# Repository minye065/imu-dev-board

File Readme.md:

\# Imu dev board

A devboard that lets you test imu programs via the onboard imu and being able to test data to it

\*Powered via the usb cable

Features:
RP2350A - MCU
ICM-42688-P - IMU

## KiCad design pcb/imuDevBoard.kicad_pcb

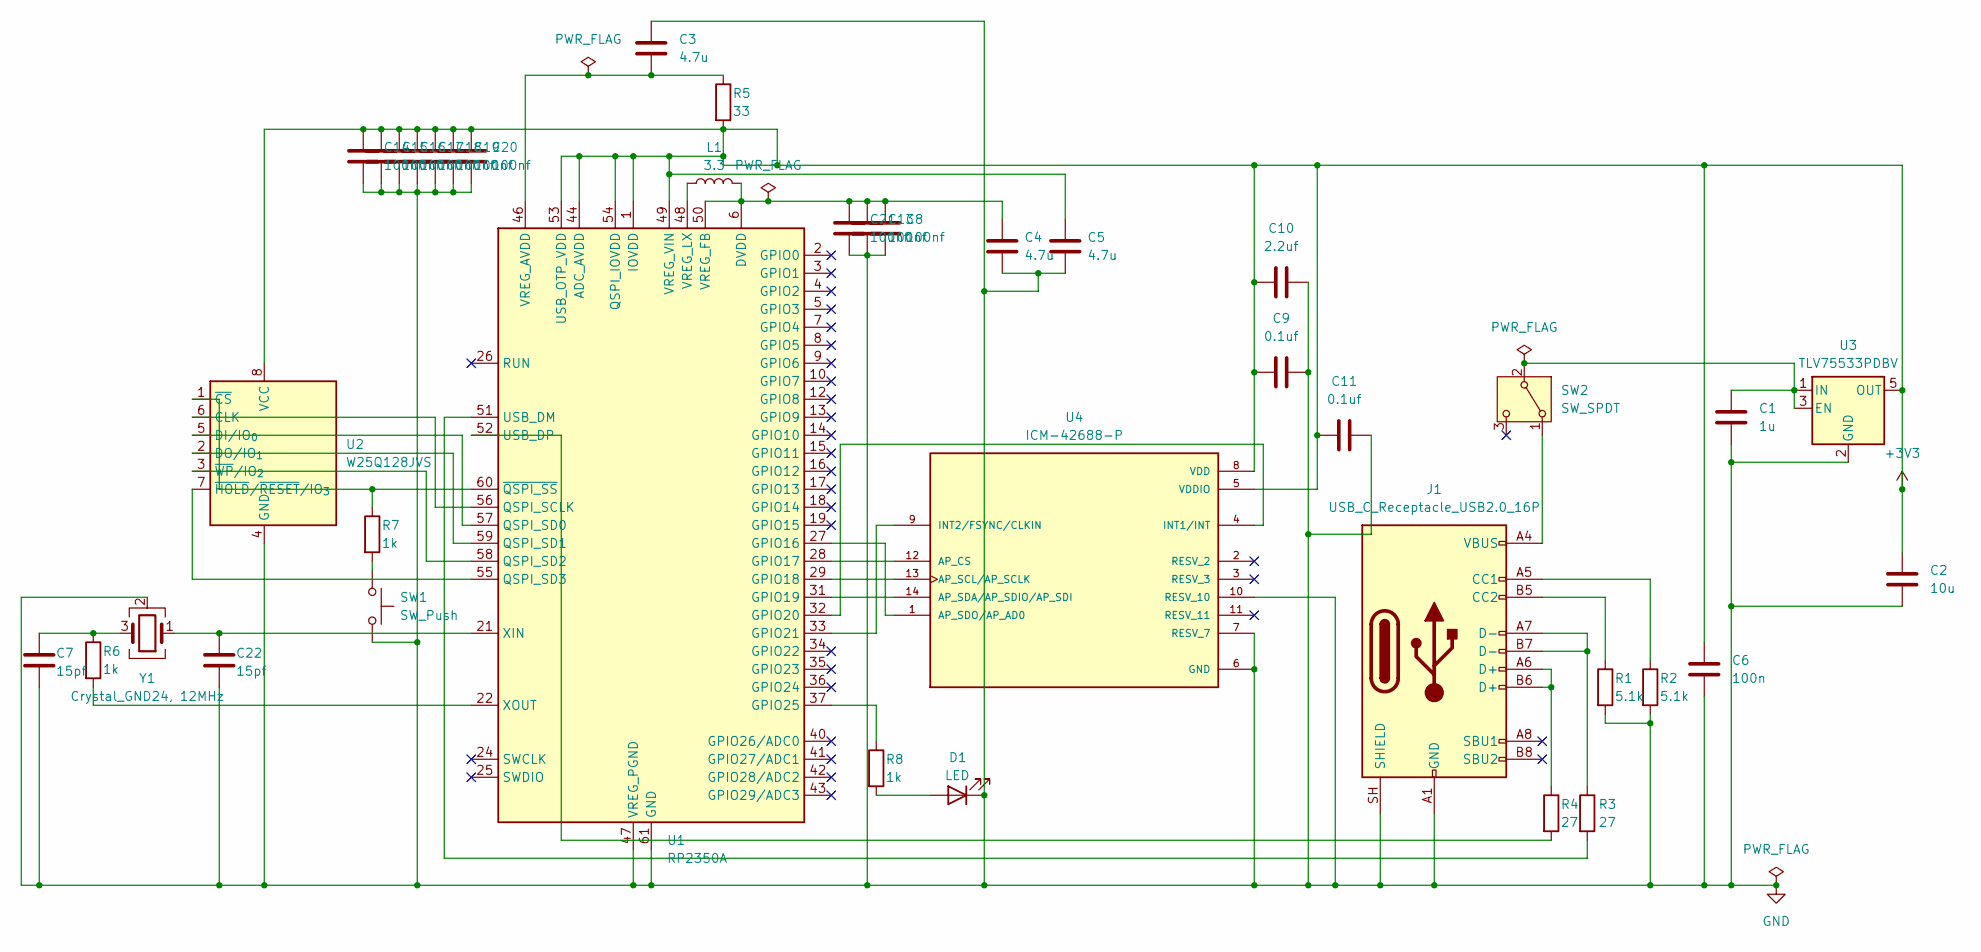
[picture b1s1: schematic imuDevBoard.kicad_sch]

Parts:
C1: 1u; C_0402_1005Metric
C2: 10u; C_0603_1608Metric
C3, C4, C5: 4.7u; C_0402_1005Metric
C6: 100n; C_0402_1005Metric
C7, C22: 15pf; C_0402_1005Metric
C8, C13, C14, C15, C16, C17, C18, C19, C20, C21: 100nf; C_0402_1005Metric
C9, C11: 0.1uf; C_0402_1005Metric
C10: 2.2uf; C_0402_1005Metric
D1: LED; LED_0603_1608Metric
J1: USB_C_Receptacle_USB2.0_16P; USB_C_Receptacle_HRO_TYPE-C-31-M-12
L1: 3.3; AOTA-B2016
R1, R2: 5.1k; R_0402_1005Metric
R3, R4: 27; R_0402_1005Metric
R5: 33; R_0402_1005Metric
R6, R7, R8: 1k; R_0402_1005Metric
SW1: SW_Push; SW_Push_1P1T_NO_Vertical_Wuerth_434133025816
SW2: SW_SPDT; SW_SPDT_Shouhan_MSK12C02
U1: RP2350A; QFN-60-1EP_7x7mm_P0.4mm_EP3.4x3.4mm
U2: W25Q128JVS; SOIC-8_5.3x5.3mm_P1.27mm
U3: TLV75533PDBV; SOT-23-5
U4: ICM-42688-P; PARTREV 1.2
Y1: Crystal_GND24, 12MHz; Crystal_SMD_3225-4Pin_3.2x2.5mm

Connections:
+3V3: C2.1, C5.2, C6.2, C9.1, C10.1, C11.1, C14.2, C15.2, C16.2, C17.2, C18.2, C19.2, C20.2, R5.2, U1.1 (IOVDD), U1.11 (IOVDD), U1.20 (IOVDD), U1.30 (IOVDD), U1.38 (IOVDD), U1.44 (ADC_AVDD), U1.45 (IOVDD), U1.49 (VREG_VIN), U1.53 (USB_OTP_VDD), U1.54 (QSPI_IOVDD), U2.8 (VCC), U3.5 (OUT), U4.5 (VDDIO), U4.8 (VDD)
GND: C1.2, C2.2, C3.1, C4.1, C5.1, C6.1, C7.1, C8.1, C9.2, C10.2, C11.2, C13.1, C14.1, C15.1, C16.1, C17.1, C18.1, C19.1, C20.1, C21.1, C22.1, D1.1 (K), J1.A1 (GND), J1.A12 (GND), J1.B1 (GND), J1.B12 (GND), J1.SH (SHIELD), R1.2, R2.2, SW1.2, U1.47 (VREG_PGND), U1.61 (GND), U2.4 (GND), U3.2 (GND), U4.6 (GND), U4.7 (RESV_7), U4.10 (RESV_10), Y1.2 (G), Y1.4 (G)
unnamed: C7.2, R6.1, Y1.3
unnamed: D1.2 (A), R8.2
unnamed: J1.A5 (CC1), R2.1
unnamed: J1.B5 (CC2), R1.1
unnamed: J1.A6 (D+), J1.B6 (D+), R4.1
unnamed: J1.A7 (D-), J1.B7 (D-), R3.1
unnamed: R7.2, SW1.1
unnamed: J1.A4 (VBUS), J1.A9 (VBUS), J1.B4 (VBUS), J1.B9 (VBUS), SW2.1 (A)
unnamed: C1.1, SW2.2 (B), U3.1 (IN), U3.3 (EN)
unnamed: U1.27 (GPIO16), U4.1 (AP_SDO/AP_AD0)
unnamed: U1.28 (GPIO17), U4.12 (AP_CS)
unnamed: U1.29 (GPIO18), U4.13 (AP_SCL/AP_SCLK)
unnamed: U1.31 (GPIO19), U4.14 (AP_SDA/AP_SDIO/AP_SDI)
unnamed: U1.32 (GPIO20), U4.4 (INT1/INT)
unnamed: U1.33 (GPIO21), U4.9 (INT2/FSYNC/CLKIN)
unnamed: R8.1, U1.37 (GPIO25)
unnamed: U1.56 (QSPI_SCLK), U2.6 (CLK)
unnamed: U1.57 (QSPI_SD0), U2.5 (DI/IO_{0})
unnamed: U1.59 (QSPI_SD1), U2.2 (DO/IO_{1})
unnamed: U1.58 (QSPI_SD2), U2.3 (~WP/IO_{2})
unnamed: U1.55 (QSPI_SD3), U2.7 (~HOLD/~RESET/IO_{3})
unnamed: R3.2, U1.51 (USB_DM)
unnamed: R4.2, U1.52 (USB_DP)
unnamed: C3.2, R5.1, U1.46 (VREG_AVDD)
unnamed: C4.2, C8.2, C13.2, C21.2, L1.2, U1.6 (DVDD), U1.23 (DVDD), U1.39 (DVDD), U1.50 (VREG_FB)
unnamed: L1.1, U1.48 (VREG_LX)
unnamed: C22.2, U1.21 (XIN), Y1.1
unnamed: R6.2, U1.22 (XOUT)
unnamed: R7.1, U1.60 (~QSPI_SS), U2.1 (~CS)

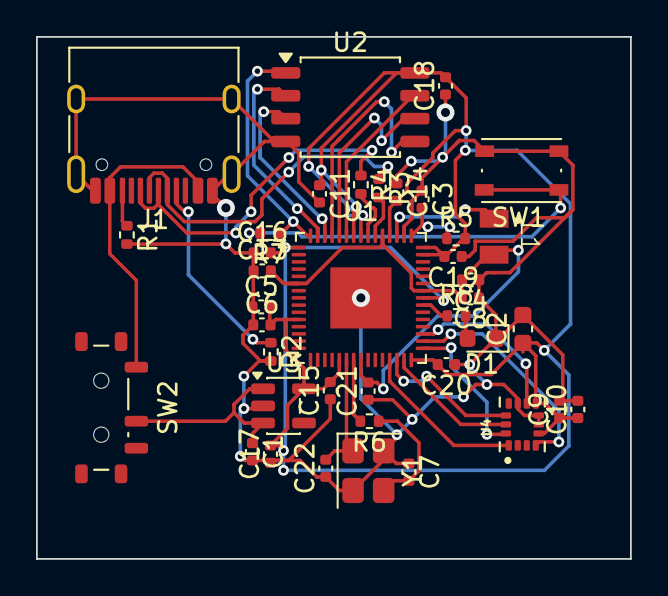
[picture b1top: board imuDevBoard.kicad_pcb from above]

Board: 2 copper layers, 33.0 x 29.0 mm, 39 parts (0 on the bottom side), 31 nets.

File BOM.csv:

"Reference","Qty","Value","DNP","Exclude from BOM","Exclude from Board","Exclude from Simulation","Exclude from Position Files","Footprint","Datasheet"
"C1","1","1u","","","","","${EXCLUDE_FROM_POS_FILES}","Capacitor_SMD:C_0402_1005Metric",""
"C2","1","10u","","","","","${EXCLUDE_FROM_POS_FILES}","Capacitor_SMD:C_0603_1608Metric",""
"C3,C4,C5","3","4.7u","","","","","${EXCLUDE_FROM_POS_FILES}","Capacitor_SMD:C_0402_1005Metric",""
"C6","1","100n","","","","","${EXCLUDE_FROM_POS_FILES}","Capacitor_SMD:C_0402_1005Metric",""
"C7,C22","2","15pf","","","","","${EXCLUDE_FROM_POS_FILES}","Capacitor_SMD:C_0402_1005Metric",""
"C8,C13,C14,C15,C16,C17,C18,C19,C20,C21","10","100nf","","","","","${EXCLUDE_FROM_POS_FILES}","Capacitor_SMD:C_0402_1005Metric",""
"C9,C11","2","0.1uf","","","","","${EXCLUDE_FROM_POS_FILES}","Capacitor_SMD:C_0402_1005Metric",""
"C10","1","2.2uf","","","","","${EXCLUDE_FROM_POS_FILES}","Capacitor_SMD:C_0402_1005Metric",""
"D1","1","LED","","","","","${EXCLUDE_FROM_POS_FILES}","LED_SMD:LED_0603_1608Metric",""
"J1","1","USB_C_Receptacle_USB2.0_16P","","","","","${EXCLUDE_FROM_POS_FILES}","Connector_USB:USB_C_Receptacle_HRO_TYPE-C-31-M-12","https://www.usb.org/sites/default/files/documents/usb_type-c.zip"
"L1","1","3.3","","","","","${EXCLUDE_FROM_POS_FILES}","kicad-includes:AOTA-B2016",""
"R1,R2","2","5.1k","","","","","${EXCLUDE_FROM_POS_FILES}","Resistor_SMD:R_0402_1005Metric",""
"R3,R4","2","27","","","","","${EXCLUDE_FROM_POS_FILES}","Resistor_SMD:R_0402_1005Metric",""
"R5","1","33","","","","","${EXCLUDE_FROM_POS_FILES}","Resistor_SMD:R_0402_1005Metric",""
"R6,R7,R8","3","1k","","","","","${EXCLUDE_FROM_POS_FILES}","Resistor_SMD:R_0402_1005Metric",""
"SW1","1","SW_Push","","","","","${EXCLUDE_FROM_POS_FILES}","Button_Switch_SMD:SW_Push_1P1T_NO_Vertical_Wuerth_434133025816",""
"SW2","1","SW_SPDT","","","","","${EXCLUDE_FROM_POS_FILES}","Button_Switch_SMD:SW_SPDT_Shouhan_MSK12C02",""
"U1","1","RP2350A","","","","","${EXCLUDE_FROM_POS_FILES}","Package_DFN_QFN:QFN-60-1EP_7x7mm_P0.4mm_EP3.4x3.4mm","https://datasheets.raspberrypi.com/rp2350/rp2350-datasheet.pdf"
"U2","1","W25Q128JVS","","","","","${EXCLUDE_FROM_POS_FILES}","Package_SO:SOIC-8_5.3x5.3mm_P1.27mm","https://www.winbond.com/resource-files/w25q128jv_dtr%20revc%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"
"U3","1","TLV75533PDBV","","","","","${EXCLUDE_FROM_POS_FILES}","Package_TO_SOT_SMD:SOT-23-5","http://www.ti.com/lit/ds/symlink/tlv755p.pdf"
"U4","1","ICM-42688-P","","","","","${EXCLUDE_FROM_POS_FILES}","kicad-includes:ICM-42688-P",""
"Y1","1","Crystal_GND24, 12MHz","","","","","${EXCLUDE_FROM_POS_FILES}","Crystal:Crystal_SMD_3225-4Pin_3.2x2.5mm",""
